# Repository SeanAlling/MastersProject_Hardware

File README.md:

# Overview 

Contains within this repository are the hardware files used for my masters project. One will find two sub directories

1. PrimaryPCB
1. TestBed

## Primary  PCB

This folder contains main PCB developed for the masters project. 

## Testbed 

This folder contain a PCB that can be used to simplify running experiments with the primary PCB.

# Special Thanks

<table><tr>
<td>  </td>
<td>  </td>
</tr></table>

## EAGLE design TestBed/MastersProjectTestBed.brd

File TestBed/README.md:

# Overview

The testbed project was designed to make reading test points simpler. Pogo pins are laid  out such that they align with a test pad on the primary PCB. The testbed also uses right angle header pins located to the sides of the PCB to allow probing signals. 

# Test Points

| TestPoint     | Description   |
| ------------- |:-------------:|
| 1             | +BAT|
| 2             | GND|
| 3             | VCC_USB|
| 4             | VCC_HDC1080|
| 5             | VCC_OPT3001|
| 6             | VCC_FPGA|
| 7             | VCC_XBEE|
| 8             | VCC_MEMORY|
| 9             | VCC_DISPLAY|
| 10            | VCC_MCU|
| 11            | GND|
| 12            | GND|
| 13            | GND|
| 14            | GND|
| 15            | GND|
| 16            | GND|
| 17            | GND|
| 18            | GND|
| 19            | <span style="text-decoration:overline">RST</span>|
| 20            | N$139|
| 21            | N$131|
| 22            | UART_TX_XBEE|
| 23            | UART_RX_XBEE|
| 24            | SPI_CLK|
| 25            | CHARGE_STATUS|
| 26            | SPI_MOSI|
| 27            | DISPLAY_D/<span style="text-decoration:overline">C</span>|
| 28            | SPI_CS_DISPLAY|
| 29            | MCU_SCL|
| 30            | MCU_SDA|
| 31            | EINK_<span style="text-decoration:overline">RST</span>|
| 32            | EINK_BUSY|
| 33            | <span style="text-decoration:overline">FLASH_WP</span>|
| 34            | FRAM_WP|
| 35            | <span style="text-decoration:overline">FLASH_HOLD</span>|
| 36            | MCU_SPI_MISO|
| 37            | MCU_SPI_CS|
| 38            | MCU_SPI_CLK|
| 39            | SPI_MOSI|
| 40            | <span style="text-decoration:overline">RTC_IN1</span>|
| 41            | RTC_CLKOUT|
| 42            | <span style="text-decoration:overline">RTC_INT2</span>|

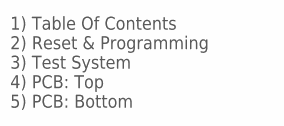
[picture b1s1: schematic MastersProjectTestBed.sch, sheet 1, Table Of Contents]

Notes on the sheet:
1) Table Of Contents 2) Reset & Programming 3) Test System 4) PCB: Top 5) PCB: Bottom

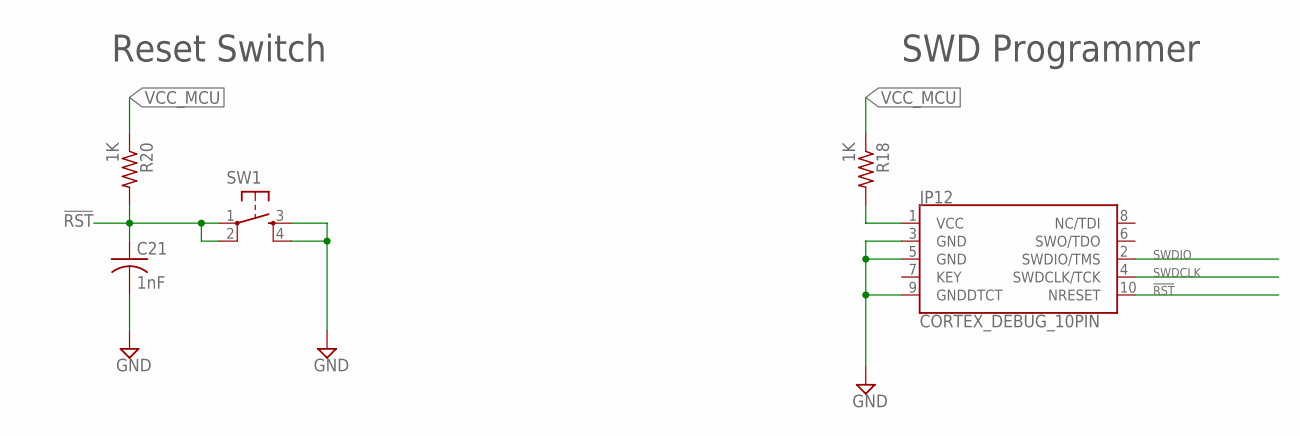
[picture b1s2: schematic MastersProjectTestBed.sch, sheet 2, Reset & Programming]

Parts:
C21: 1nF; C0603; PARTNO 08053F102K4T2A
JP12: CORTEX_DEBUG_10PIN; PARTNO 3220-10-0100-00
R18, R20: 1K; R0603; PARTNO RC0805JR-071KL
SW1: TACTILE-SWITCH-SMT; 7914G; PARTNO 7914G-1-000E

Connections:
!RST: C21.1, JP12.10 (NRESET), R20.2, SW1.1, SW1.2
GND: C21.2, JP12.3 (GND), JP12.5 (GND), JP12.9 (GNDDTCT), SW1.3, SW1.4; also elsewhere on the board
unnamed: JP12.1 (VCC), R18.2
SWDCLK: JP12.4 (SWDCLK/TCK); also elsewhere on the board
SWDIO: JP12.2 (SWDIO/TMS); also elsewhere on the board
VCC_MCU: R18.1, R20.1; also elsewhere on the board

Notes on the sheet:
SWD Programmer
Reset Switch

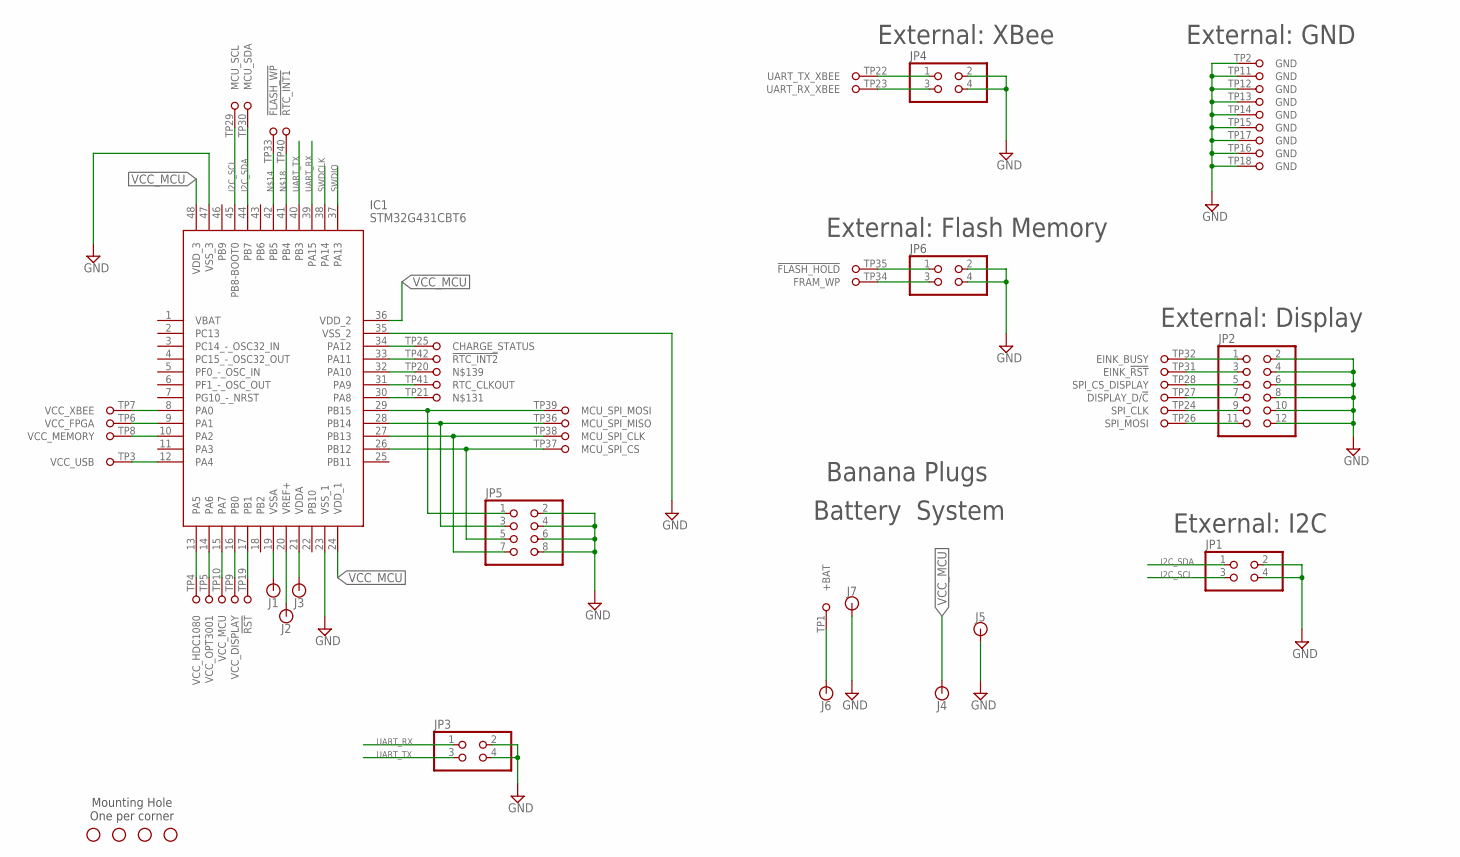
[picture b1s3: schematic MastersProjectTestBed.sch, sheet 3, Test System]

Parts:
H1, H2, H3, H4: STAND-OFF
IC1: STM32G431CBT6; QFP50P900X900X160-48N
J1, J2, J3, J4, J5, J6, J7: BANANA_CONN
JP1, JP3, JP4, JP6: PINHD-2X2/90; 2X02/90
JP2: PINHD-2X6/90; 2X06/90
JP5: PINHD-2X4/90; 2X04/90
TP1: PCB-POGO

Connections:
GND: IC1.23 (VSS_1), IC1.35 (VSS_2), IC1.47 (VSS_3), J5.P$1, J7.P$1, JP1.2, JP1.4, JP2.2, JP2.4, JP2.6, JP2.8, JP2.10, JP2.12, JP3.2, JP3.4, JP4.2, JP4.4, JP5.2, JP5.4, JP5.6, JP5.8, JP6.2, JP6.4, TP1.TP2 (GND), TP1.TP11 (GND), TP1.TP12 (GND), TP1.TP13 (GND), TP1.TP14 (GND), TP1.TP15 (GND), TP1.TP16 (GND), TP1.TP17 (GND), TP1.TP18 (GND); also elsewhere on the board
I2C_SCL: IC1.45 (PB8-BOOT0), JP1.3, TP1.TP29 (MCU_SCL)
I2C_SDA: IC1.44 (PB7), JP1.1, TP1.TP30 (MCU_SDA)
unnamed: IC1.9 (PA1), TP1.TP6 (VCC_FPGA)
unnamed: IC1.8 (PA0), TP1.TP7 (VCC_XBEE)
unnamed: IC1.10 (PA2), TP1.TP8 (VCC_MEMORY)
unnamed: J6.P$1, TP1.TP1 (+BAT)
unnamed: IC1.12 (PA4), TP1.TP3 (VCC_USB)
unnamed: IC1.33 (PA11), TP1.TP42 (!RTC_INT2)
unnamed: IC1.34 (PA12), TP1.TP25 (CHARGE_STATUS)
unnamed: IC1.13 (PA5), TP1.TP4 (VCC_HDC1080)
unnamed: IC1.14 (PA6), TP1.TP5 (VCC_OPT3001)
unnamed: IC1.15 (PA7), TP1.TP10 (VCC_MCU)
unnamed: IC1.17 (PB1), TP1.TP19 (!RST)
unnamed: IC1.30 (PA8), TP1.TP21
unnamed: IC1.42 (PB5), TP1.TP33 (!FLASH_WP)
unnamed: JP6.1, TP1.TP35 (!FLASH_HOLD)
unnamed: JP6.3, TP1.TP34 (FRAM_WP)
unnamed: IC1.16 (PB0), TP1.TP9 (VCC_DISPLAY)
unnamed: IC1.41 (PB4), TP1.TP40 (!RTC_INT1)
unnamed: IC1.32 (PA10), TP1.TP20
unnamed: IC1.31 (PA9), TP1.TP41 (RTC_CLKOUT)
unnamed: JP2.9, TP1.TP24 (SPI_CLK)
unnamed: JP2.11, TP1.TP26 (SPI_MOSI)
unnamed: JP2.7, TP1.TP27 (DISPLAY_D/!C)
unnamed: JP2.5, TP1.TP28 (SPI_CS_DISPLAY)
unnamed: JP2.3, TP1.TP31 (EINK_!RST)
unnamed: JP2.1, TP1.TP32 (EINK_BUSY)
unnamed: JP4.1, TP1.TP22 (UART_TX_XBEE)
unnamed: JP4.3, TP1.TP23 (UART_RX_XBEE)
unnamed: IC1.29 (PB15), JP5.1, TP1.TP39 (MCU_SPI_MOSI)
unnamed: IC1.28 (PB14), JP5.3, TP1.TP36 (MCU_SPI_MISO)
unnamed: IC1.27 (PB13), JP5.7, TP1.TP38 (MCU_SPI_CLK)
unnamed: IC1.26 (PB12), JP5.5, TP1.TP37 (MCU_SPI_CS)
unnamed: IC1.19 (VSSA), J1.P$1
unnamed: IC1.20 (VREF+), J2.P$1
unnamed: IC1.21 (VDDA), J3.P$1
SWDCLK: IC1.38 (PA14); also elsewhere on the board
SWDIO: IC1.37 (PA13); also elsewhere on the board
UART_RX: IC1.39 (PA15), JP3.1
UART_TX: IC1.40 (PB3), JP3.3
VCC_MCU: IC1.24 (VDD_1), IC1.36 (VDD_2), IC1.48 (VDD_3), J4.P$1; also elsewhere on the board

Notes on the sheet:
Mounting Hole One per corner
External: GND
External: Display
Etxernal: I2C
External: XBee
External: Flash Memory
Banana Plugs
Battery
System

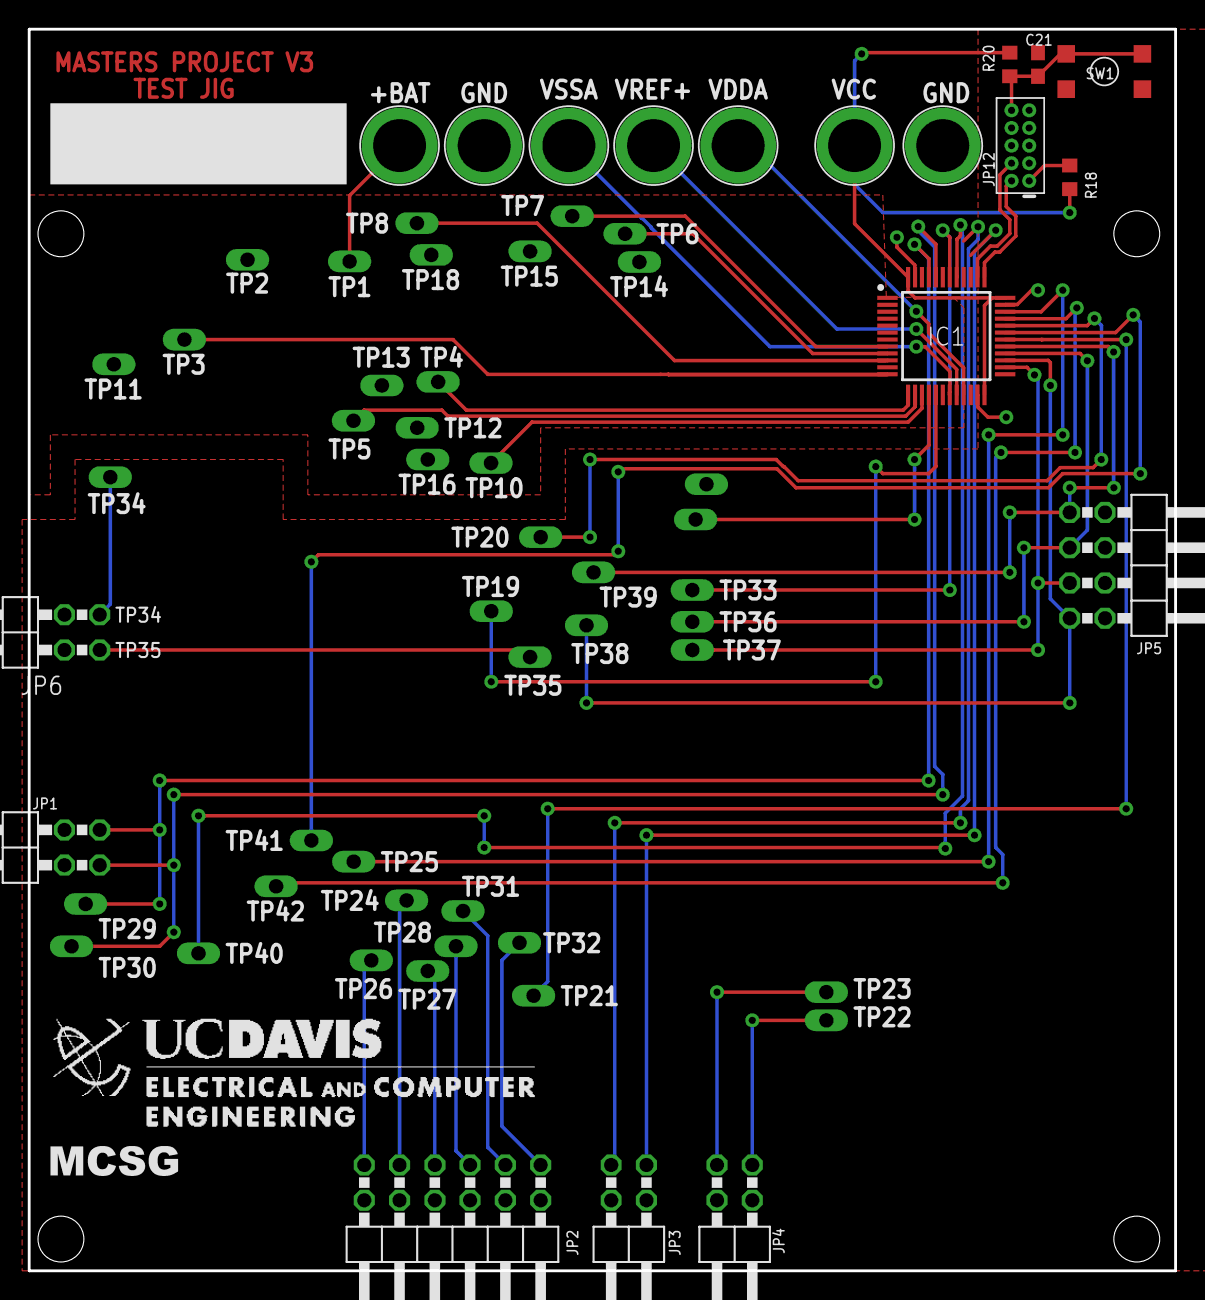
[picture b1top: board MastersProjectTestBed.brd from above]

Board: 2 copper layers, 82.5 x 89.4 mm, 27 parts (1 on the bottom side), 44 nets.

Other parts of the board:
U$1: UC_DAVIS_ENG
U$2: MCSG_SMALL
U$3: UC_DAVIS_EEC

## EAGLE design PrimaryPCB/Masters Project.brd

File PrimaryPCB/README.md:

# Overview

The project enclosed is the final version designed, developed, assembled, and tested for my Masters project at UC Davis. 

# Dependencies

This project was developed using EagleCAD 9.4.2. Different versions of eagle are not guaranteed to work.

__NOTE__: Libraries are not provided. Only the schematic and PCB project files are included.

# Project Structure

## BOM (Bill Of Material)

The BOM folder contains two different BOMs. First is a standard bill of material and contains an itemized list of the parts used in the project. 

A second BOM call iBOM (interactive BOM) is included that can be used to help find part placement during assembly.

## Documentation

Documentation folder contains a single PDF. The PDF contains all schematics, along with renderings of the top and bottom of the PCB, and images of each layer. 

## Gerbers

Contains a zip file that can be used for ordering the PCB from a manufacturer.

## Images

Raw images that are used in Documentation PDF.

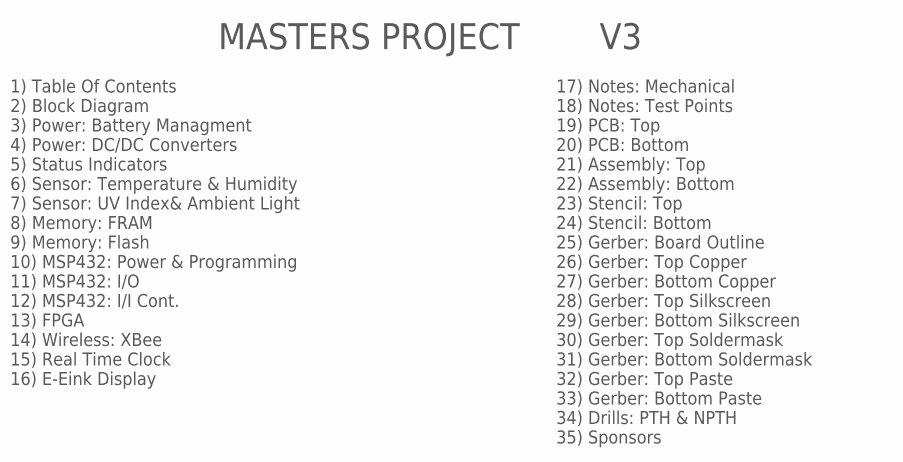
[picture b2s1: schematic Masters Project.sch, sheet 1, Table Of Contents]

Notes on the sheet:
MASTERS PROJECT
1) Table Of Contents 2) Block Diagram 3) Power: Battery Managment 4) Power: DC/DC Converters 5) Status Indicators 6) Sensor: Temperature & Humidity 7) Sensor: UV Index& Ambient Light 8) Memory: FRAM 9) Memory: Flash 10) MSP432: Power & Programming 11) MSP432: I/O 12) MSP432: I/I Cont. 13) FPGA 14) 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
17) Notes: Mechanical 18) Notes: Test Points 19) PCB: Top 20) PCB: Bottom 21) Assembly: Top 22) Assembly: Bottom 23) Stencil: Top 24) Stencil: Bottom 25) Gerber: Board Outline 26) Gerber: Top Copper 27) Gerber: Bottom Copper 28) Gerber: Top Silkscreen 29) Gerber: Bottom Silkscreen 30) Gerber: Top S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

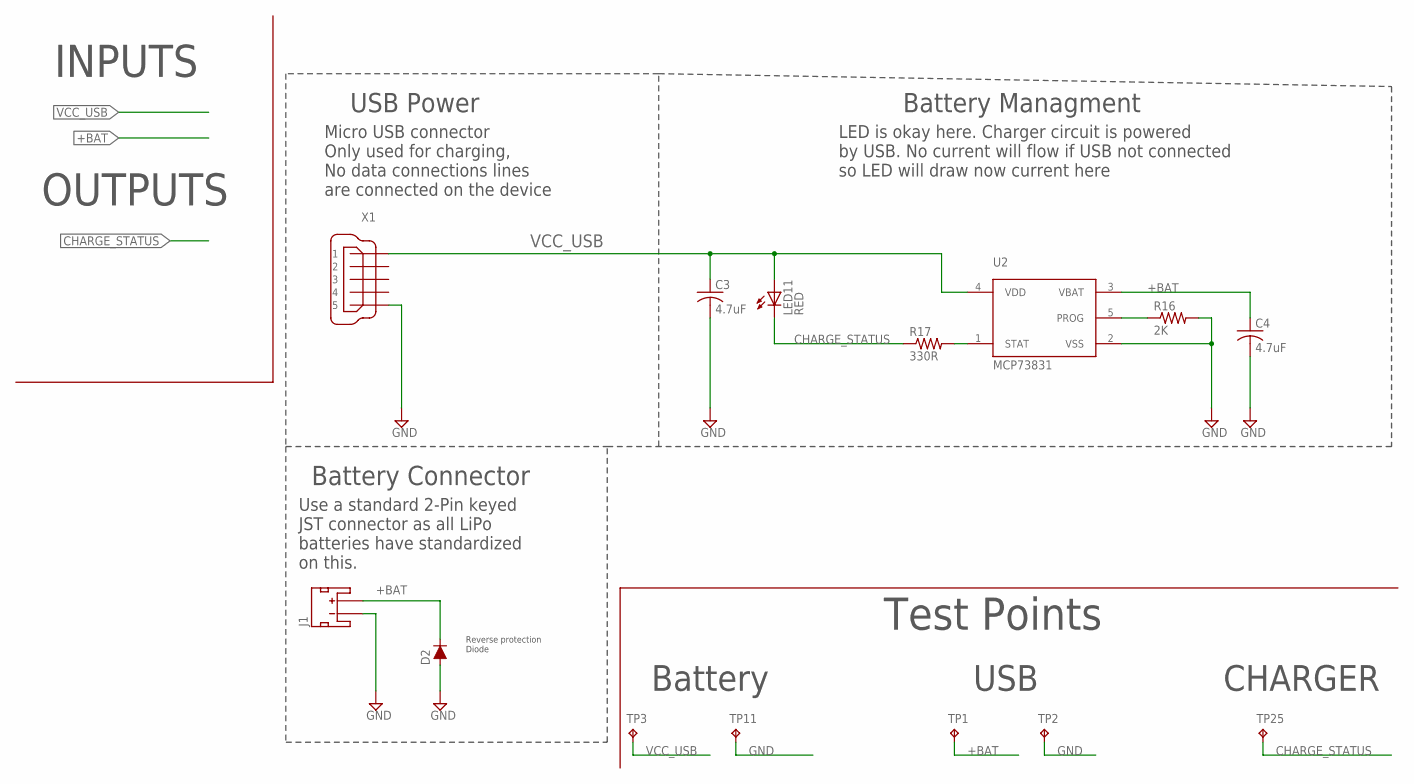
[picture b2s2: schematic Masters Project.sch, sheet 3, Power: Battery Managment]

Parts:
C3, C4: 4.7uF; C0603; PARTNO CL21A475KBQNNNE
D2: 250mA/100V; SOD-323
J1: JST_2MM_MALE; JST-2-SMD; PARTNO S2B-PH-SM4-TB(LF)(SN)
LED11: RED; CHIPLED_0603; PARTNO LG R971-KN-1
R16: 2K; R0603; PARTNO RC0805FR-072KL
R17: 330R; R0603; PARTNO RMCF0805JT330R
TP1, TP2, TP3, TP11, TP25: TPB1,27; B1,27
U2: MCP73831; SOT23-5L; PARTNO MCP73831T-2ATI/OT
X1: MINI-USB-32005-201; 32005-201; PARTNO 10033526-N3212LF

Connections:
+BAT: C4.1, D2.C, J1.2 (+), TP1.TP, U2.3 (VBAT); also elsewhere on the board
CHARGE_STATUS: LED11.C, R17.1, TP25.TP; also elsewhere on the board
GND: C3.2, C4.2, D2.A, J1.1 (-), R16.2, TP2.TP, TP11.TP, U2.2 (VSS), X1.5; also elsewhere on the board
unnamed: R17.2, U2.1 (STAT)
unnamed: R16.1, U2.5 (PROG)
VCC_USB: C3.1, LED11.A, TP3.TP, U2.4 (VDD), X1.1; also elsewhere on the board

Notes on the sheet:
Battery Managment
Battery Connector
USB Power
Micro USB connector Only used for charging, No data connections lines are connected on the device
Reverse protection Diode
Use a standard 2-Pin keyed JST connector as all LiPo batteries have standardized on this.
Test Points
Battery
USB
CHARGER
LED is okay here. Charger circuit is powered by USB. No current will flow if USB not connected so LED will draw now current here
INPUTS
OUTPUTS

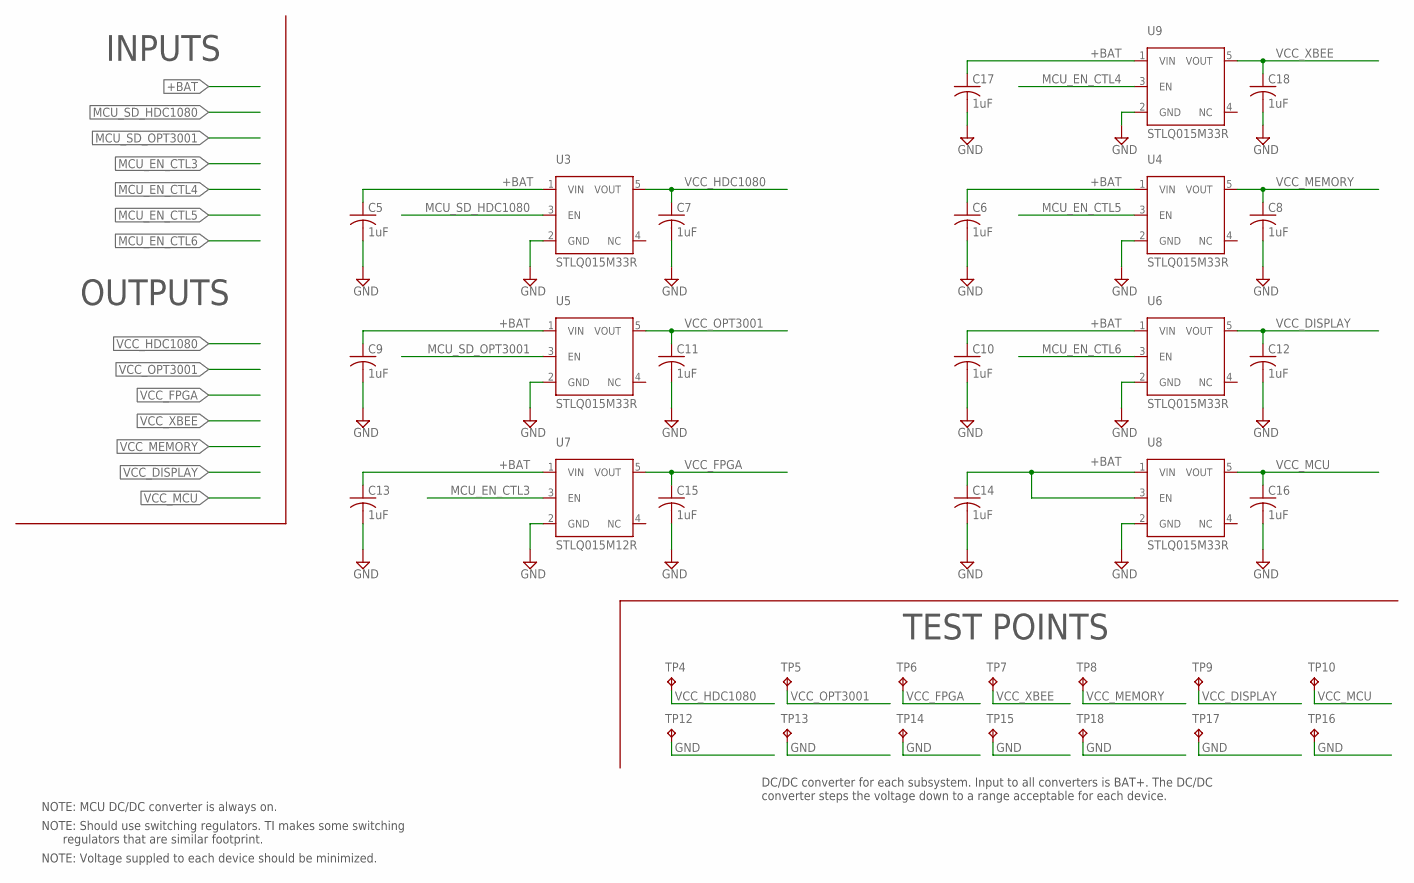
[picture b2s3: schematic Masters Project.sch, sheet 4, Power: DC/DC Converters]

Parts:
C5, C6, C7, C8, C9, C10, C11, C12, C13, C14, C15, C16, C17, C18: 1uF; C0603; PARTNO CC0805ZKY5V9BB105
TP4, TP5, TP6, TP7, TP8, TP9, TP10, TP12, TP13, TP14, TP15, TP16, TP17, TP18: TPB1,27; B1,27
U3, U5, U6, U8, U9: STLQ015M33R; SOT23-5L; PARTNO STLQ015M33R
U4: STLQ015M33R; SOT23-5L; PARTNO STLQ015M12R
U7: STLQ015M12R; SOT23-5L; PARTNO STLQ015M12R

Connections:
+BAT: C5.1, C6.1, C9.1, C10.1, C13.1, C14.1, C17.1, U3.1 (VIN), U4.1 (VIN), U5.1 (VIN), U6.1 (VIN), U7.1 (VIN), U8.1 (VIN), U8.3 (EN), U9.1 (VIN); also elsewhere on the board
GND: C5.2, C6.2, C7.2, C8.2, C9.2, C10.2, C11.2, C12.2, C13.2, C14.2, C15.2, C16.2, C17.2, C18.2, TP12.TP, TP13.TP, TP14.TP, TP15.TP, TP16.TP, TP17.TP, TP18.TP, U3.2 (GND), U4.2 (GND), U5.2 (GND), U6.2 (GND), U7.2 (GND), U8.2 (GND), U9.2 (GND); also elsewhere on the board
MCU_EN_CTL3: U7.3 (EN); also elsewhere on the board
MCU_EN_CTL4: U9.3 (EN); also elsewhere on the board
MCU_EN_CTL5: U4.3 (EN); also elsewhere on the board
MCU_EN_CTL6: U6.3 (EN); also elsewhere on the board
MCU_SD_HDC1080: U3.3 (EN); also elsewhere on the board
MCU_SD_OPT3001: U5.3 (EN); also elsewhere on the board
VCC_DISPLAY: C12.1, TP9.TP, U6.5 (VOUT); also elsewhere on the board
VCC_FPGA: C15.1, TP6.TP, U7.5 (VOUT); also elsewhere on the board
VCC_HDC1080: C7.1, TP4.TP, U3.5 (VOUT); also elsewhere on the board
VCC_MCU: C16.1, TP10.TP, U8.5 (VOUT); also elsewhere on the board
VCC_MEMORY: C8.1, TP8.TP, U4.5 (VOUT); also elsewhere on the board
VCC_OPT3001: C11.1, TP5.TP, U5.5 (VOUT); also elsewhere on the board
VCC_XBEE: C18.1, TP7.TP, U9.5 (VOUT); also elsewhere on the board

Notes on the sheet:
DC/DC converter for each subsystem. Input to all converters is BAT+. The DC/DC converter steps the voltage down to a range acceptable for each device.
TEST POINTS
INPUTS
OUTPUTS
NOTE: MCU DC/DC converter is always on.
NOTE: Should use switching regulators. TI makes some switching regulators that are similar footprint.
NOTE: Voltage suppled to each device should be minimized.

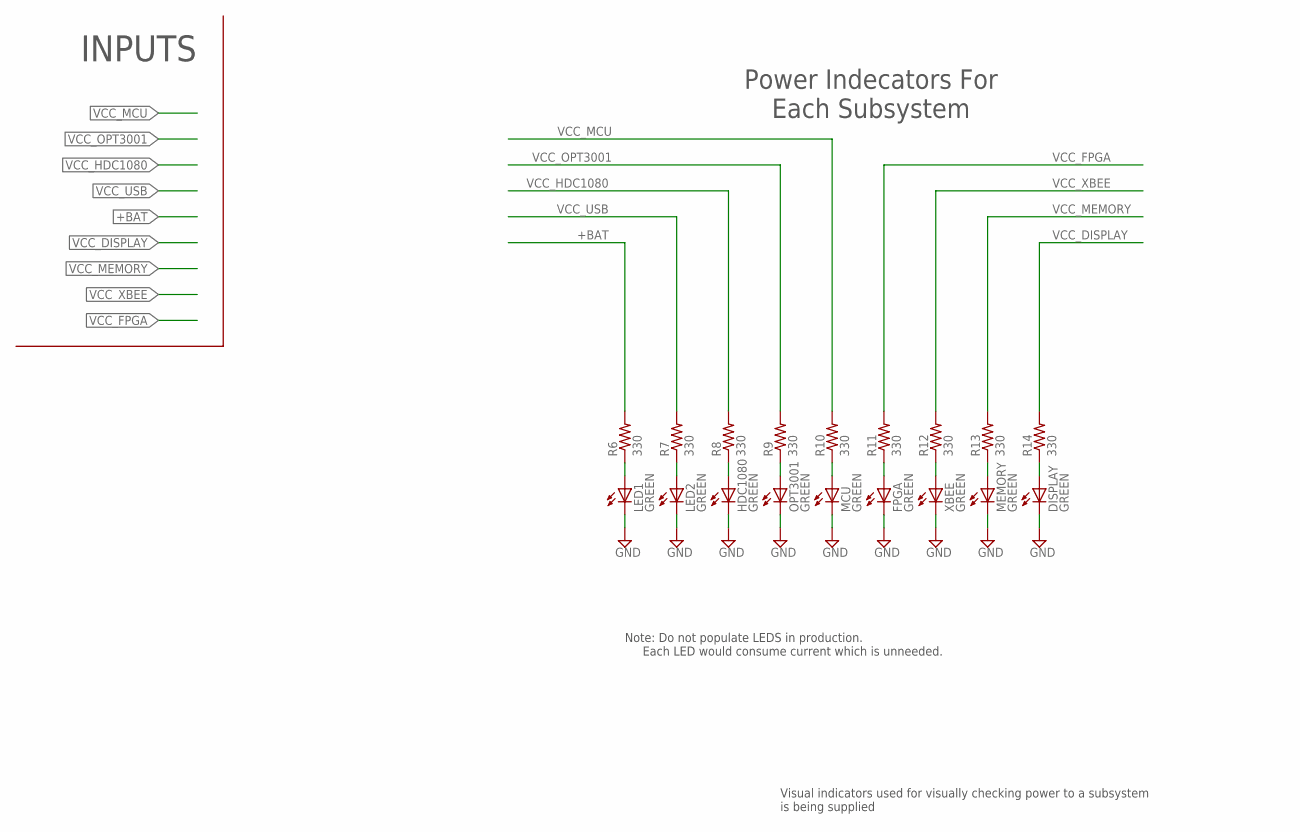
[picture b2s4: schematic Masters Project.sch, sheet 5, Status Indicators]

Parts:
DISPLAY: GREEN; CHIPLED_0603; PARTNO LG R971-KN-1
FPGA: GREEN; CHIPLED_0603; PARTNO LG R971-KN-1
HDC1080: GREEN; CHIPLED_0603; PARTNO LG R971-KN-1
LED1, LED2: GREEN; CHIPLED_0603; PARTNO LG R971-KN-1
MCU: GREEN; CHIPLED_0603; PARTNO LG R971-KN-1
MEMORY: GREEN; CHIPLED_0603; PARTNO LG R971-KN-1
OPT3001: GREEN; CHIPLED_0603; PARTNO LG R971-KN-1
R6, R7, R8, R9, R10, R11, R12, R13, R14: 330; R0603; PARTNO RMCF0805JT330R
XBEE: GREEN; CHIPLED_0603; PARTNO LG R971-KN-1

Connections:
+BAT: R6.2; also elsewhere on the board
GND: DISPLAY.C, FPGA.C, HDC1080.C, LED1.C, LED2.C, MCU.C, MEMORY.C, OPT3001.C, XBEE.C; also elsewhere on the board
unnamed: LED1.A, R6.1
unnamed: LED2.A, R7.1
unnamed: HDC1080.A, R8.1
unnamed: OPT3001.A, R9.1
unnamed: MCU.A, R10.1
unnamed: FPGA.A, R11.1
unnamed: DISPLAY.A, R14.1
unnamed: MEMORY.A, R13.1
unnamed: R12.1, XBEE.A
VCC_DISPLAY: R14.2; also elsewhere on the board
VCC_FPGA: R11.2; also elsewhere on the board
VCC_HDC1080: R8.2; also elsewhere on the board
VCC_MCU: R10.2; also elsewhere on the board
VCC_MEMORY: R13.2; also elsewhere on the board
VCC_OPT3001: R9.2; also elsewhere on the board
VCC_USB: R7.2; also elsewhere on the board
VCC_XBEE: R12.2; also elsewhere on the board

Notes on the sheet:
Power Indecators For Each Subsystem
INPUTS
Visual indicators used for visually checking power to a subsystem is being supplied
Note: Do not populate LEDS in production. Each LED would consume current which is unneeded.

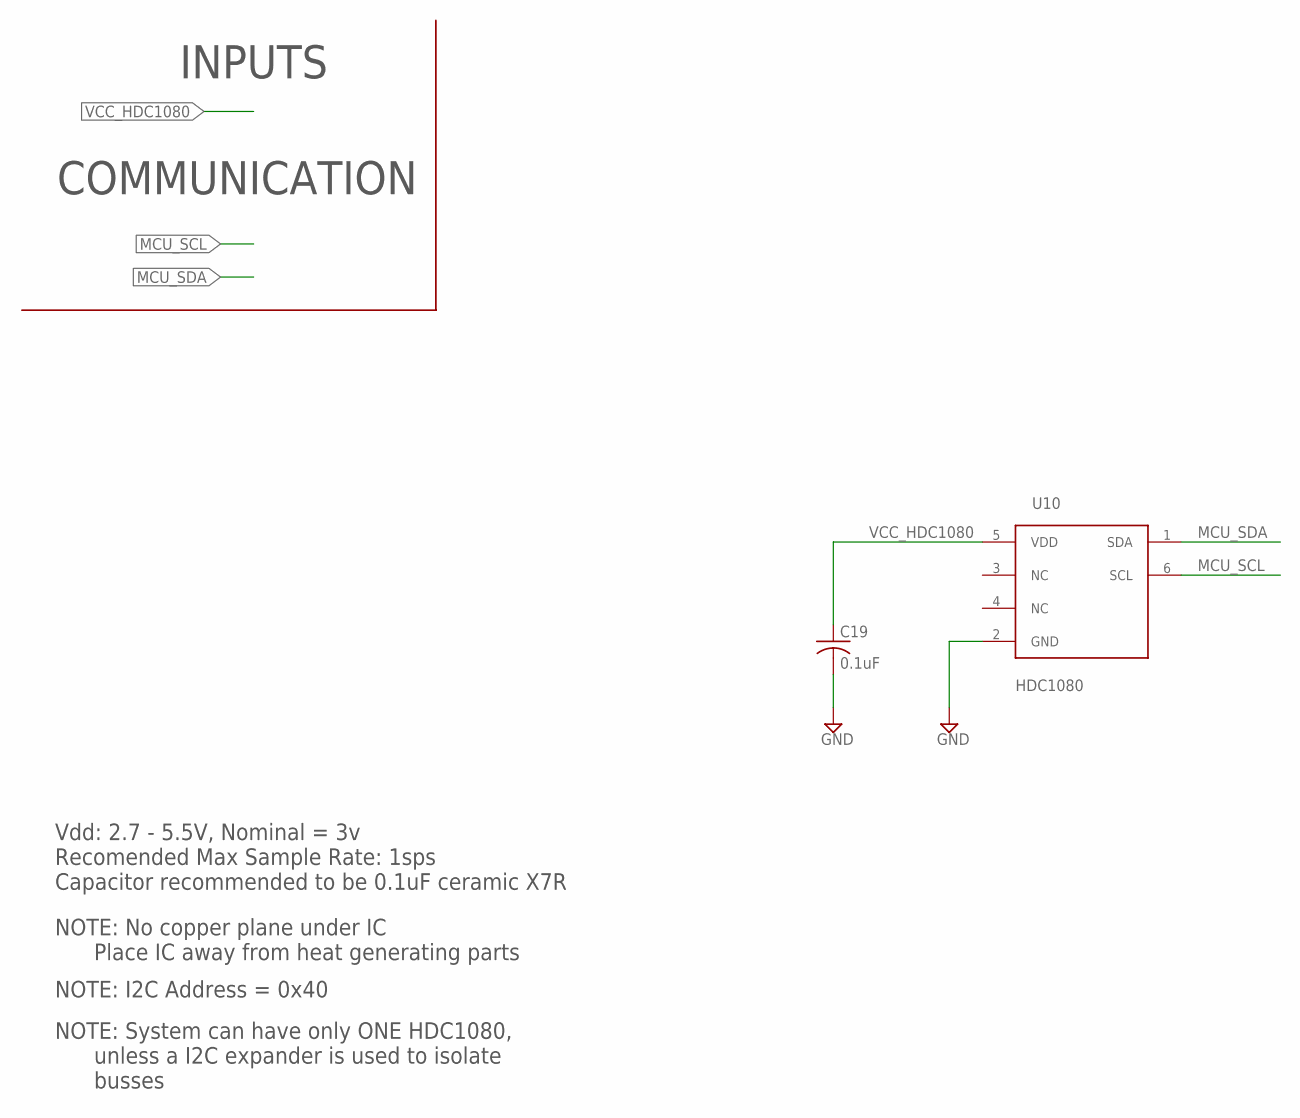
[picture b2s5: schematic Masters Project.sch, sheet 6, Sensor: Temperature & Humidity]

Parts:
C19: 0.1uF; C0603; PARTNO 08055C104KAT2A
U10: HDC1080; WSON-6; PARTNO HDC1080DMBT

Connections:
GND: C19.2, U10.2 (GND); also elsewhere on the board
MCU_SCL: U10.6 (SCL); also elsewhere on the board
MCU_SDA: U10.1 (SDA); also elsewhere on the board
VCC_HDC1080: C19.1, U10.5 (VDD); also elsewhere on the board

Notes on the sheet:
Vdd: 2.7 - 5.5V, Nominal = 3v Recomended Max Sample Rate: 1sps Capacitor recommended to be 0.1uF ceramic X7R
NOTE: No copper plane under IC Place IC away from heat generating parts
INPUTS
COMMUNICATION
NOTE: I2C Address = 0x40
NOTE: System can have only ONE HDC1080, unless a I2C expander is used to isolate busses

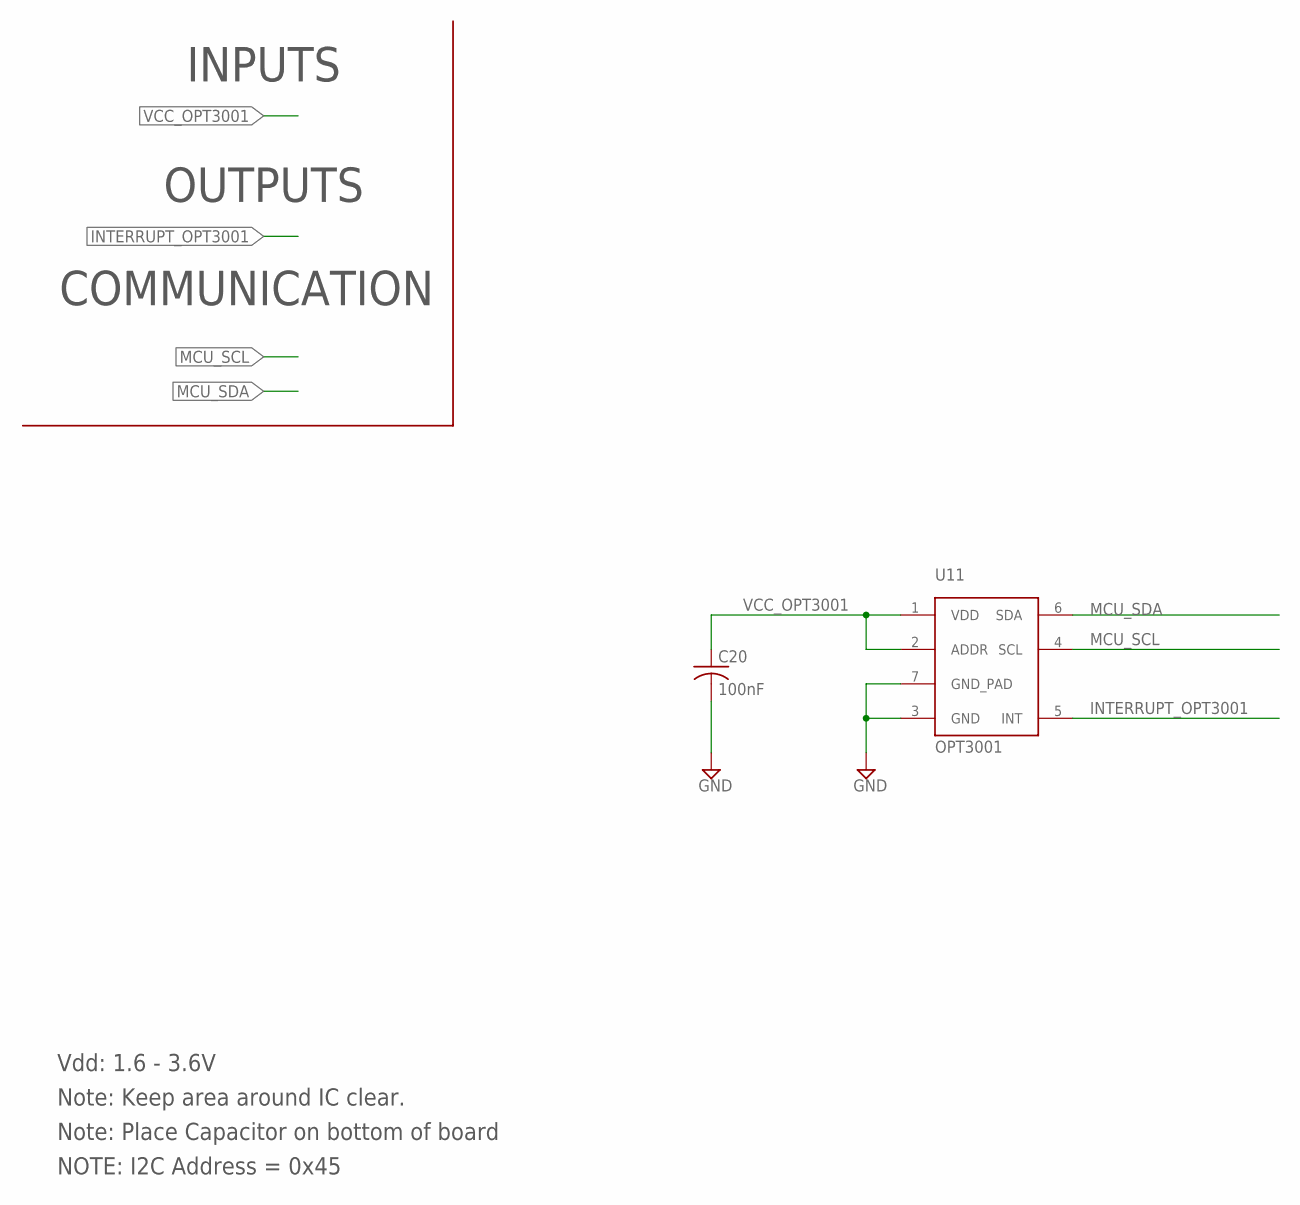
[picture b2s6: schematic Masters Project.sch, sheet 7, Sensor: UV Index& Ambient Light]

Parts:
C20: 100nF; C0603; PARTNO CC0603ZRY5V9BB104
U11: OPT3001; USON-6; PARTNO OPT3001DNPT

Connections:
GND: C20.2, U11.3 (GND), U11.7 (GND_PAD); also elsewhere on the board
INTERRUPT_OPT3001: U11.5 (INT); also elsewhere on the board
MCU_SCL: U11.4 (SCL); also elsewhere on the board
MCU_SDA: U11.6 (SDA); also elsewhere on the board
VCC_OPT3001: C20.1, U11.1 (VDD), U11.2 (ADDR); also elsewhere on the board

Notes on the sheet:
Vdd: 1.6 - 3.6V
Note: Keep area around IC clear.
INPUTS
COMMUNICATION
OUTPUTS
Note: Place Capacitor on bottom of board
NOTE: I2C Address = 0x45

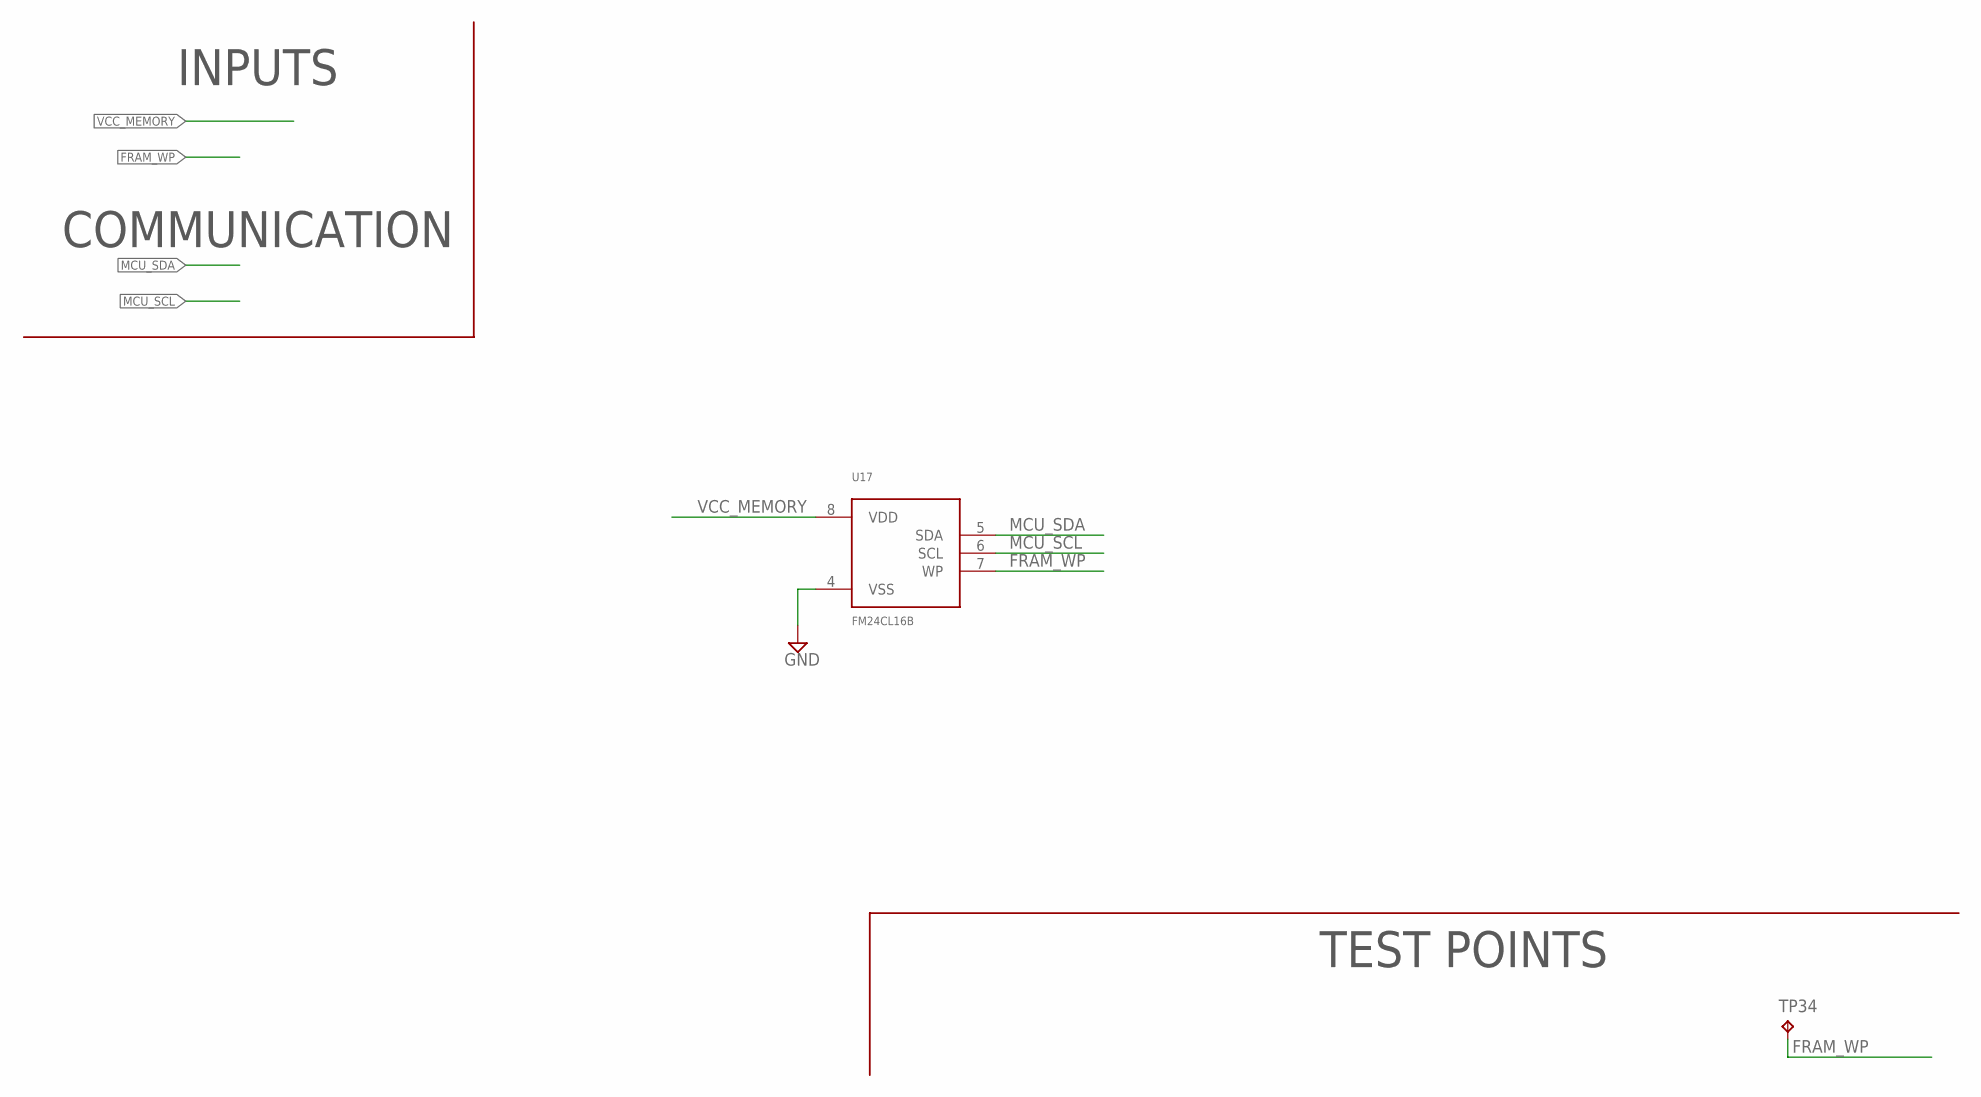
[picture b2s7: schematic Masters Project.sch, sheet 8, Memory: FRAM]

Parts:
TP34: TPB1,27; B1,27
U17: FM24CL16B

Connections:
FRAM_WP: TP34.TP, U17.7 (WP); also elsewhere on the board
GND: U17.4 (VSS); also elsewhere on the board
MCU_SCL: U17.6 (SCL); also elsewhere on the board
MCU_SDA: U17.5 (SDA); also elsewhere on the board
VCC_MEMORY: U17.8 (VDD); also elsewhere on the board

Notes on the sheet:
INPUTS
COMMUNICATION
TEST POINTS

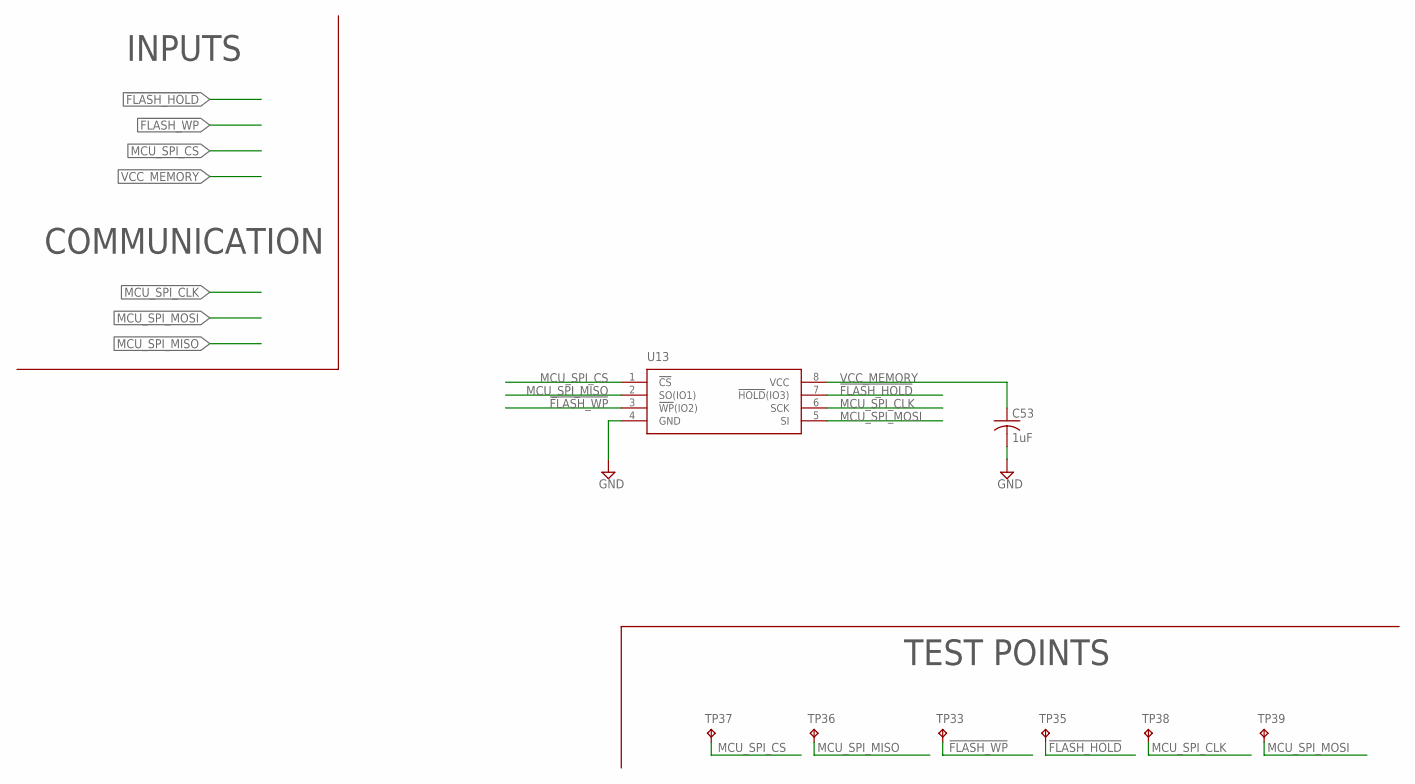
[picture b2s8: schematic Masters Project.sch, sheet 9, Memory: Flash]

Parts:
C53: 1uF; C0603; PARTNO C0805C220J5GACTU
TP33, TP35, TP36, TP37, TP38, TP39: TPB1,27; B1,27
U13: AT25SL128A; SON127P600X500X60-8N

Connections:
!FLASH_HOLD: TP35.TP, U13.7 (!HOLD!(IO3)); also elsewhere on the board
!FLASH_WP: TP33.TP, U13.3 (!WP!(IO2)); also elsewhere on the board
GND: C53.2, U13.4 (GND); also elsewhere on the board
MCU_SPI_CLK: TP38.TP, U13.6 (SCK); also elsewhere on the board
MCU_SPI_CS: TP37.TP, U13.1 (!CS); also elsewhere on the board
MCU_SPI_MISO: TP36.TP, U13.2 (SO(IO1)); also elsewhere on the board
MCU_SPI_MOSI: TP39.TP, U13.5 (SI); also elsewhere on the board
VCC_MEMORY: C53.1, U13.8 (VCC); also elsewhere on the board

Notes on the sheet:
TEST POINTS
INPUTS
COMMUNICATION

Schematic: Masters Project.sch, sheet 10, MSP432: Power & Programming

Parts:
C21: 1nF; C0603; PARTNO 08053F102K4T2A
C22, C23, C24, C25: 22pF; C0603; PARTNO C0805C220J5GACTU
C26, C29, C31, C33, C35: 100nF; C0603; PARTNO CC0603ZRY5V9BB104
C27: 4uF; C0603; PARTNO C0805C395K8PACTU
C28, C30, C32, C34: 4.7uF; C0603; PARTNO CL21A475KBQNNNE
JP12: CORTEX_DEBUG_10PIN; PARTNO 3220-10-0100-00
L1: 4.7uH; L-USL0805; PARTNO BRC2012T4R7MD
Q1: CPFBZ-A2C4-32.768KD6; PARTNO CPFBZ-A2C4-32.768KD6
Q2: ABM8-48.000MHZ-B2-T; CRYSTAL_4-SMD; PARTNO ABM8-48.000MHZ-B2-T
R18, R20: 1K; R0603; PARTNO RC0805JR-071KL
R26: 91k; R0603; PARTNO RC0805JR-0791KL
SW1: TACTILE-SWITCH-SMT; 7914G; PARTNO 7914G-1-000E
TP19, TP20, TP21: TPB1,27; B1,27
U12: MSP432P401R; LQFP100; PARTNO MSP432P401RIPZR

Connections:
!RST: C21.1, JP12.10 (NRESET), R20.2, SW1.1, SW1.2, TP19.TP, U12.83 (RSTN/NMI)
FREQ_HF: C24.1, Q2.P$1 (1), TP20.TP, U12.85 (PJ.2/HFXOUT)
FREQ_LF: C22.1, Q1.P$1 (1), TP21.TP, U12.41 (PJ.0/LFXIN)
GND: C21.2, C22.2, C23.2, C24.2, C25.2, C26.2, C27.2, C28.2, C29.2, C30.2, C31.2, C32.2, C33.2, C34.2, C35.2, JP12.3 (GND), JP12.5 (GND), JP12.9 (GNDDTCT), R26.1, SW1.3, SW1.4, U12.15 (DVSS1), U12.40 (AVSS3), U12.43 (AVSS1), U12.72 (DVSS2), U12.82 (DVSS3), U12.84 (AVSS2); also elsewhere on the board
unnamed: JP12.1 (VCC), R18.2
unnamed: R26.2, U12.44 (DCOR)
unnamed: L1.1, U12.14 (VSW)
unnamed: C26.1, C27.1, L1.2, U12.12 (VCORE)
unnamed: JP12.2 (SWDIO/TMS), U12.94 (SWDIO/TMS)
unnamed: JP12.6 (SWO/TDO), U12.93 (PJ.5/TDO/SWO)
unnamed: JP12.8 (NC/TDI), U12.92 (PJ.4/TDI/ADC14CLK)
unnamed: C23.1, Q1.P$4 (2), U12.42 (PJ.1/LFXOUT)
unnamed: JP12.4 (SWDCLK/TCK), U12.95 (SWCLK/TCK)
unnamed: C25.1, Q2.P$3 (2), U12.86 (PJ.3/HFXIN)
VCC_MCU: C28.1, C29.1, C30.1, C31.1, C32.1, C33.1, C34.1, C35.1, R18.1, R20.1, U12.13 (DVCC1), U12.45 (AVCC1), U12.73 (DVCC2), U12.87 (AVCC2); also elsewhere on the board

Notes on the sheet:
External JTAG/SWD To MCU & Low/Hogh Frequency Crystals
NOTE: 100nF decoupling capacitor should be a low-ESR ceramic
NOTE: L = LQM21PN4R7NGR
Reset Switch
Power
DVCC2
DVCC1
AVCC1
AVCC2
INPUTS
TEST POINTS
OUTPUTS
Decoupling
NOTE: Place as close to indicated pins as possible
NOTE: !RST line also uses internal R of MCU for filtering
NOTE: R18 Used for current limiting

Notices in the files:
parts and their libraries:
SparkFun-Connectors: Licensing: Creative Commons ShareAlike 4.0 International - https://creativecommons.org/licenses/by-sa/4.0
